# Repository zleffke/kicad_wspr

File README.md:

# kicad_wspr
KiCAD designs for WSPR Transmitters

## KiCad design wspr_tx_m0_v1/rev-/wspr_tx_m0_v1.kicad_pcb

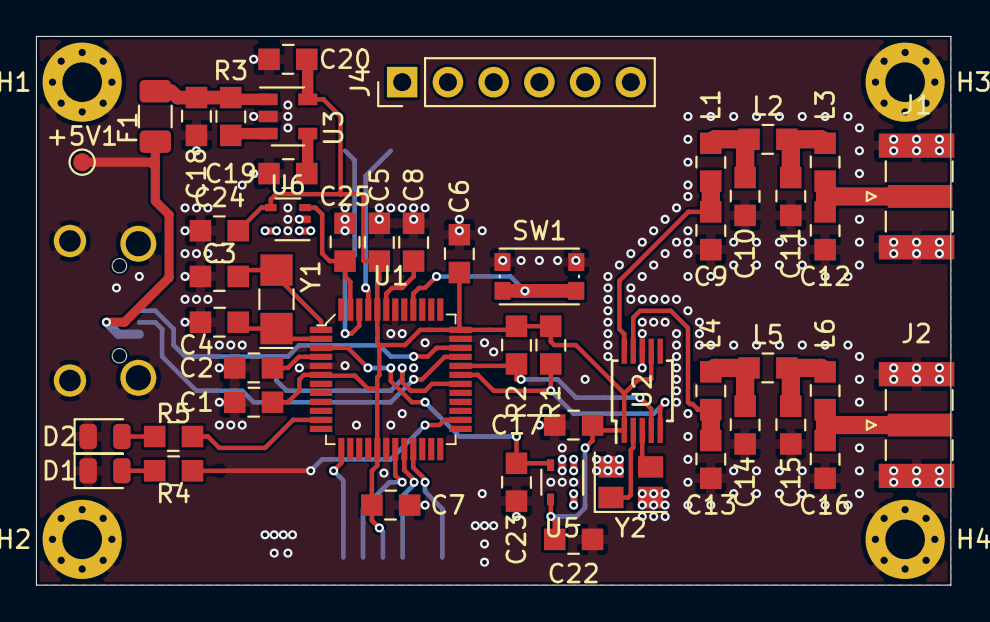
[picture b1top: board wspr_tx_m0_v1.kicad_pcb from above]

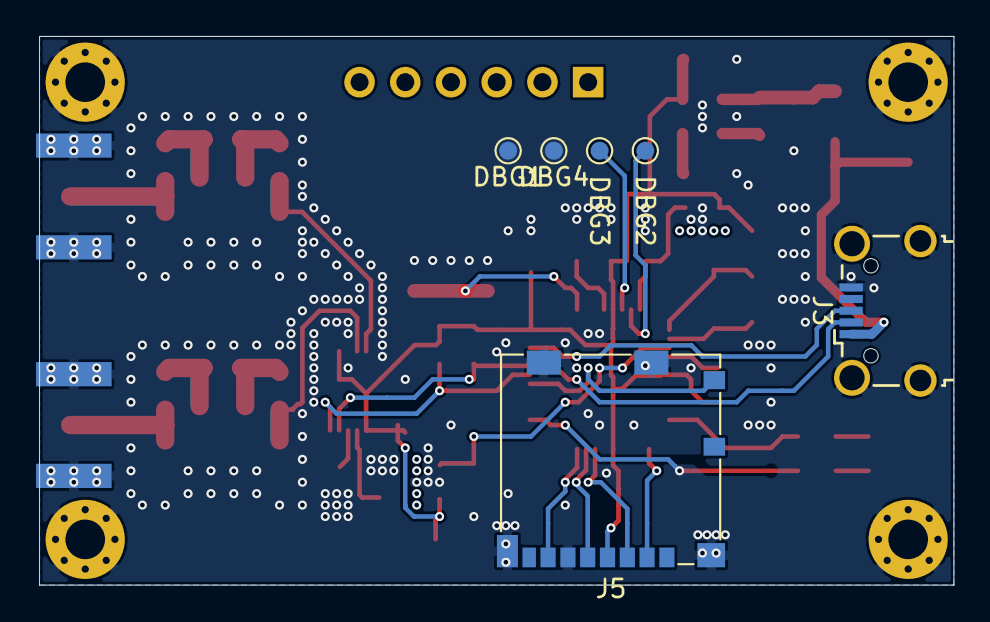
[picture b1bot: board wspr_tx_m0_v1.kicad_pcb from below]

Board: 2 copper layers, 50.8 x 30.5 mm, 60 parts (6 on the bottom side), 38 nets.

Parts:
+5V1: +5V; TestPoint_Pad_D1.0mm
C1, C2, C5, C6, C7, C8, C17, C19, C20, C22, C23, C24, C25: 1uF; 0805
C3, C4: 22pF; 0805
C9, C10, C11, C12, C13, C14, C15, C16: C; 0805
C18: 10uF; 0805
D1: RED; LED_0805_2012Metric
D2: GRN; LED_0805_2012Metric
DBG1: VREF; TestPoint_Pad_D1.0mm
DBG2: SWDIO; TestPoint_Pad_D1.0mm
DBG3: SWCLK; TestPoint_Pad_D1.0mm
DBG4: GND; TestPoint_Pad_D1.0mm
F1: Polyfuse; Fuse_1206_3216Metric
H1, H2, H3, H4: MountingHole_Pad; MountingHole_2.2mm_M2_Pad_Via
J1: RF1; SMA_Samtec_SMA-J-P-X-ST-EM1_EdgeMount
J2: RF2; SMA_Samtec_SMA-J-P-X-ST-EM1_EdgeMount
J3: USB_B_Micro; USB_Micro-B_Wuerth_629105150521_CircularHoles
J4: Conn_01x06_Male; PinHeader_1x06_P2.54mm_Vertical
J5: Micro_SD_Card_Det; microSD_HC_Molex_104031-0811
L1, L2, L3, L4, L5, L6: L; 0805
R1, R2: 4.7k; 0805
R3: 100k; 0805
R4, R5: 2.2k; 0805
SW1: SW_Push; SW_Push_1P1T_NO_CK_KMR2
U1: ATSAMD21G18A-AUT; TQFP-48_7x7mm
U2: Si5351A-B-GT; MSOP-10_3x3mm_P0.5mm
U3: SPX3819M5-L-3-3; SOT-23-5
U5, U6: MCP9700AT-ELT; SOT-353_SC-70-5
Y1: Crystal; Crystal_SMD_G8-2Pin_3.2x1.5mm_HandSoldering
Y2: Crystal_GND24; Crystal_SMD_Abracon_ABM8G-4Pin_3.2x2.5mm

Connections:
+3V3: C1.1, C5.1, C6.1, C7.1, C17.2, C20.1, C22.2, C24.2, DBG1.1, J5.4, R1.2, R2.2, U1.6, U1.17, U1.36, U1.44, U2.1, U2.7, U3.5, U5.4, U6.4
+5V: C18.1, F1.1, R3.2, U3.1
/A0: C23.2, U1.3, U5.3
/A5: C25.2, U1.47, U6.3
/AREF: C2.1, U1.4
/D7: J5.10, U1.30
/D8: R5.2, U1.11
/D13: R4.2, U1.26
/D+: J3.3, U1.34
/D-: J3.2, U1.33
/LPF Filters/RF1_IN: C9.1, L1.1, U2.10
/LPF Filters/RF1_OUT: C12.1, J1.1, L3.2
/LPF Filters/RF2_IN: C13.1, L4.1, U2.9
/LPF Filters/RF2_OUT: C16.1, J2.1, L6.2
/MISO: J5.7, U1.21
/MOSI: J5.3, U1.19
/SCK: J5.5, U1.20
/SCL: R2.1, U1.32, U2.4
/SDA: R1.1, U1.31, U2.5
/SD_CS: J5.2, U1.13
/SWCLK: DBG3.1, U1.45
/SWDIO: DBG2.1, U1.46
/~RESET: SW1.1, U1.40
GND: C1.2, C2.2, C3.2, C4.2, C5.2, C6.2, C7.2, C8.2, C9.2, C10.2, C11.2, C12.2, C13.2, C14.2, C15.2, C16.2, C17.1, C18.2, C19.2, C20.2, C22.1, C23.1, C24.1, C25.1, D1.1, D2.1, DBG4.1, H1.1, H2.1, H3.1, H4.1, J1.2, J2.2, J3.5, J3.6, J5.6, J5.11, SW1.2, U1.5, U1.18, U1.35, U1.42, U2.8, U3.2, U5.2, U6.2, Y2.2, Y2.4
unnamed: +5V1.1, F1.2, J3.1
unnamed: C3.1, U1.1, Y1.2
unnamed: C4.1, U1.2, Y1.1
unnamed: C8.1, U1.43
unnamed: C10.1, L1.2, L2.1
unnamed: C11.1, L2.2, L3.1
unnamed: C14.1, L4.2, L5.1
unnamed: C15.1, L5.2, L6.1
unnamed: C19.1, U3.4
unnamed: D1.2, R4.1
unnamed: D2.2, R5.1
unnamed: R3.1, U3.3
unnamed: U2.2, Y2.1
unnamed: U2.3, Y2.3

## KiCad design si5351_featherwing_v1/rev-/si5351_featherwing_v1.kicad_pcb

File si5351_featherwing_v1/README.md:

# si5351_featherwing_v1
* Si5351 breakout board in Adafruit Feather form factor.
* Basically an Si5351 breakout board with Low Pass Filters between clk0 and clk1 and the SMA connectors. 
* LPFs are bypassable if external filtering is used.
* This specific version was designed to work with an [Adafruit Feather M0 Adalogger](https://www.adafruit.com/product/2796) with reference to pinouts, interrupts, etc.  May be applicable to other feathers, but the M0 Adalogger was the primary focus.
* The current version of the design also expects an Ultimate GPS featherwing (for timing alignment).

#### Revision History
| Date     | Revision | Note  |
|----------|----------|-------|
| 20200429 | rev-     | Version was submitted to osh park for first prototypes |

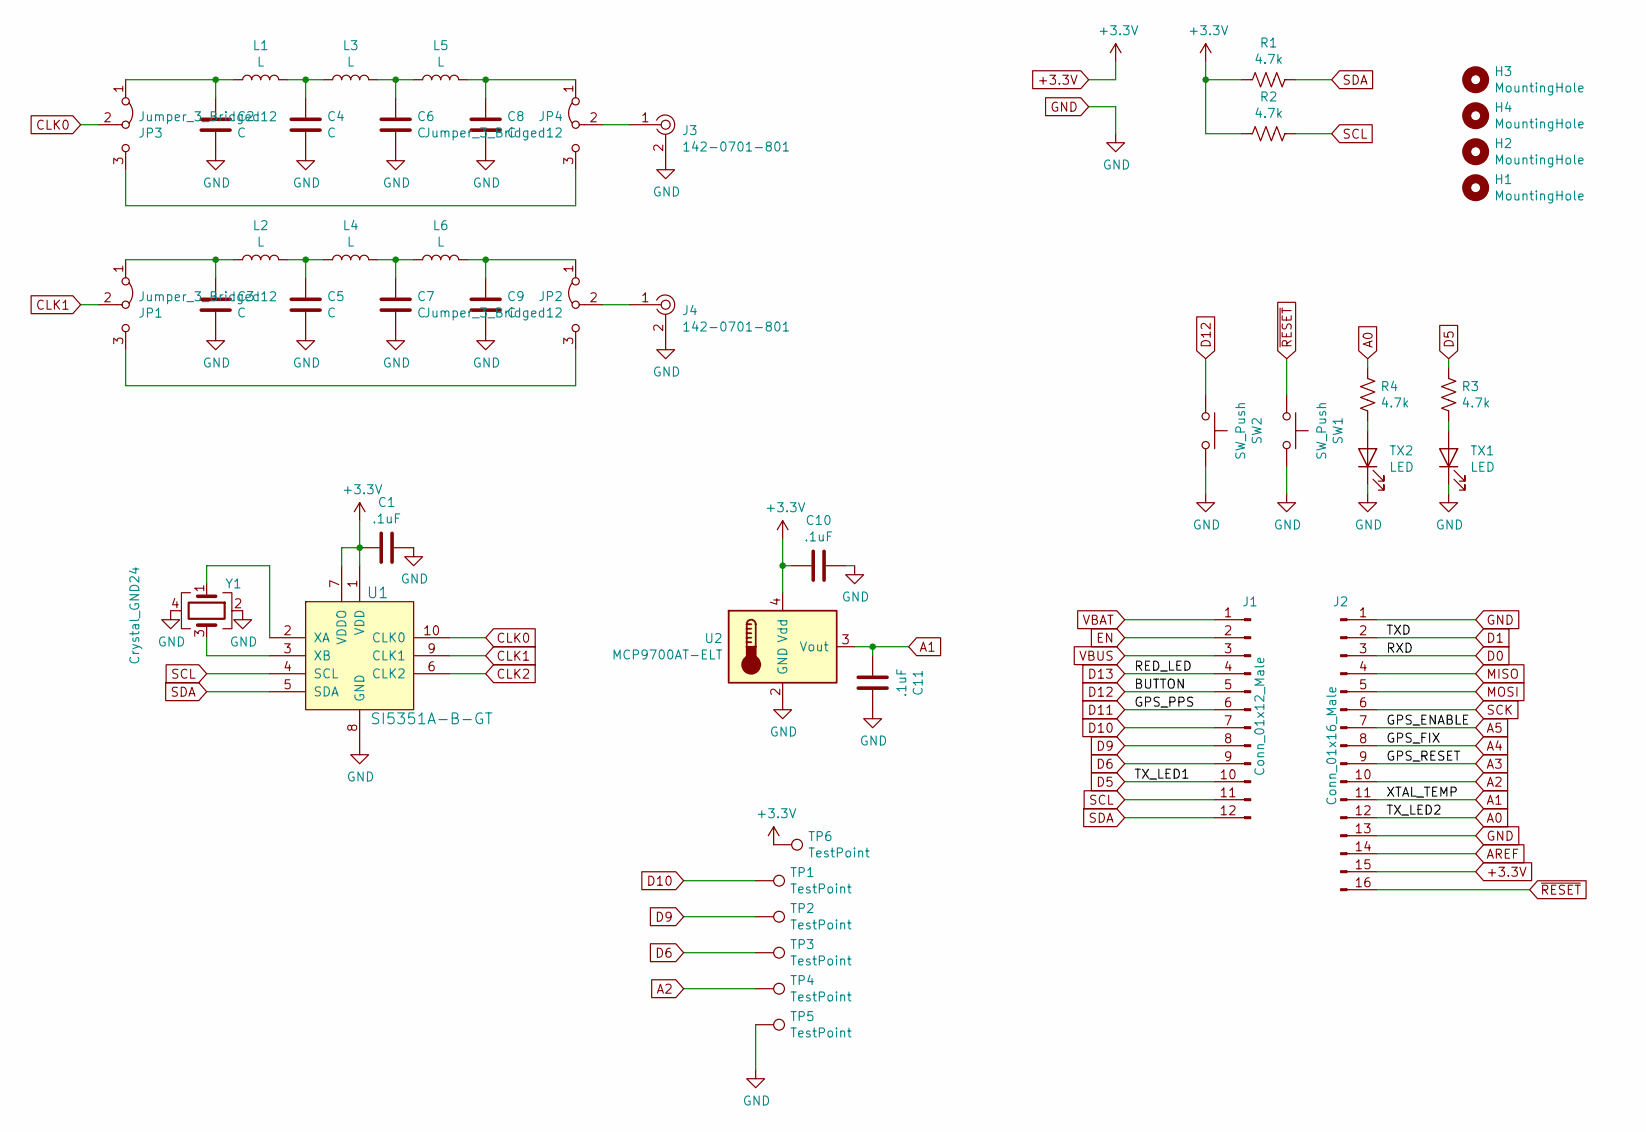
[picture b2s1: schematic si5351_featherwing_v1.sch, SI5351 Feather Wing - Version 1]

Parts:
C1, C10, C11: .1uF; 0805
C2, C3, C4, C5, C6, C7, C8, C9: C; 0805
H1, H2, H3, H4: MountingHole; MountingHole_2.5mm
J1: Conn_01x12_Male; PinHeader_1x12_P2.54mm_Vertical
J2: Conn_01x16_Male; PinHeader_1x16_P2.54mm_Vertical
J3, J4: 142-0701-801; RF_SMA_BoardEdge_142-0701-801; MPN 142-0701-801; Digi-Key_PN J502-ND
JP1, JP2, JP3, JP4: Jumper_3_Bridged12; SolderJumper-3_P1.3mm_Open_RoundedPad1.0x1.5mm_NumberLabels
L1, L2, L3, L4, L5, L6: L; 0805
R1, R2, R3, R4: 4.7k; 0805
SW1, SW2: SW_Push; SW_Push_1P1T_NO_CK_KMR2
TP1, TP2, TP3, TP4, TP5, TP6: TestPoint; TestPoint_Pad_D1.0mm
TX1, TX2: LED; LED_0805_2012Metric
U1: SI5351A-B-GT; MSOP-10_W3mm; MPN SI5351A-B-GT; Digi-Key_PN 336-2399-5-ND
U2: MCP9700AT-ELT; SOT-353_SC-70-5
Y1: Crystal_GND24; Crystal_SMD_Abracon_ABM8G-4Pin_3.2x2.5mm

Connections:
+3.3V: C1.2, C10.2, J2.15, R1.2, R2.2, TP6.1, U1.1 (VDD), U1.7 (VDDO), U2.4 (Vdd)
A0: J2.12, R4.2
A1: C11.2, J2.11, U2.3 (Vout)
A2: J2.10, TP4.1
A3: J2.9
A4: J2.8
A5: J2.7
AREF: J2.14
CLK0: JP3.2 (C), U1.10 (CLK0)
CLK1: JP1.2 (C), U1.9 (CLK1)
CLK2: U1.6 (CLK2)
D0: J2.3
D1: J2.2
D5: J1.10, R3.2
D6: J1.9, TP3.1
D9: J1.8, TP2.1
D10: J1.7, TP1.1
D11: J1.6
D12: J1.5, SW2.1
D13: J1.4
EN: J1.2
GND: C1.1, C2.2, C3.2, C4.2, C5.2, C6.2, C7.2, C8.2, C9.2, C10.1, C11.1, J2.1, J2.13, J3.2, J4.2, SW1.2, SW2.2, TP5.1, TX1.1 (K), TX2.1 (K), U1.8 (GND), U2.2 (GND), Y1.2, Y1.4
MISO: J2.4
MOSI: J2.5
unnamed: C2.1, JP3.1 (A), L1.1
unnamed: C3.1, JP1.1 (A), L2.1
unnamed: C4.1, L1.2, L3.1
unnamed: C5.1, L2.2, L4.1
unnamed: C6.1, L3.2, L5.1
unnamed: C7.1, L4.2, L6.1
unnamed: C8.1, JP4.1 (A), L5.2
unnamed: C9.1, JP2.1 (A), L6.2
unnamed: J3.1, JP4.2 (C)
unnamed: J4.1, JP2.2 (C)
unnamed: JP1.3 (B), JP2.3 (B)
unnamed: JP3.3 (B), JP4.3 (B)
unnamed: R3.1, TX1.2 (A)
unnamed: R4.1, TX2.2 (A)
unnamed: U1.2 (XA), Y1.1
unnamed: U1.3 (XB), Y1.3
SCK: J2.6
SCL: J1.11, R2.1, U1.4 (SCL)
SDA: J1.12, R1.1, U1.5 (SDA)
VBAT: J1.1
VBUS: J1.3
~RESET: J2.16, SW1.1

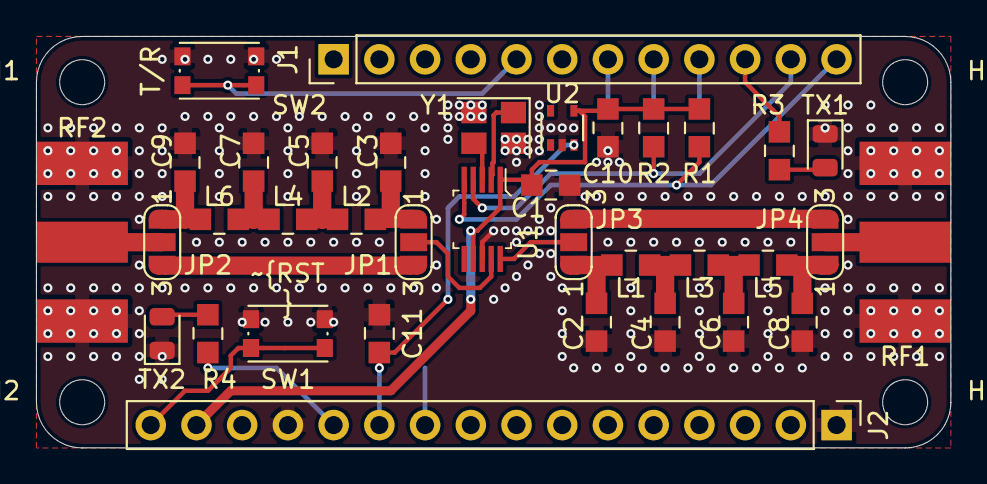
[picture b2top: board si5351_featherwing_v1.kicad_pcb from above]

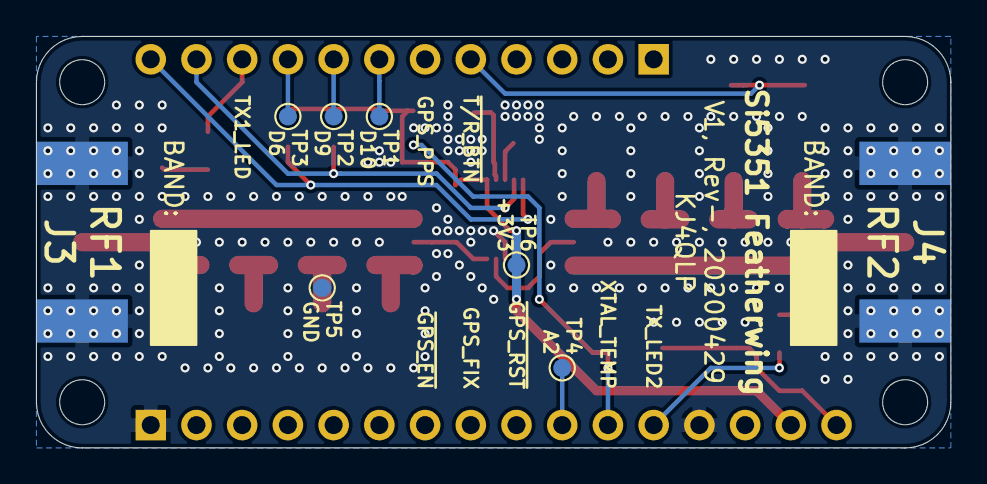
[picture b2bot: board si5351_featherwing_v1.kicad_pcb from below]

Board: 2 copper layers, 50.8 x 22.9 mm, 46 parts (6 on the bottom side), 31 nets.

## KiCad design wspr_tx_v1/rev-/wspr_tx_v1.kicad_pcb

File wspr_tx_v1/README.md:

# kicad_wspr_tx_v1
Basically an Si5351 breakout board with Low Pass Filters between all three clock outputs and the SMA connectors.

Taken from [Adafruit Si5351 Breakout EagleCAD design](https://github.com/adafruit/Adafruit-Si5351A-Clock-Generator-Breakout-PCB) but ported to KiCAD and LPFs added.

This version was designed but not actually built - 2020424

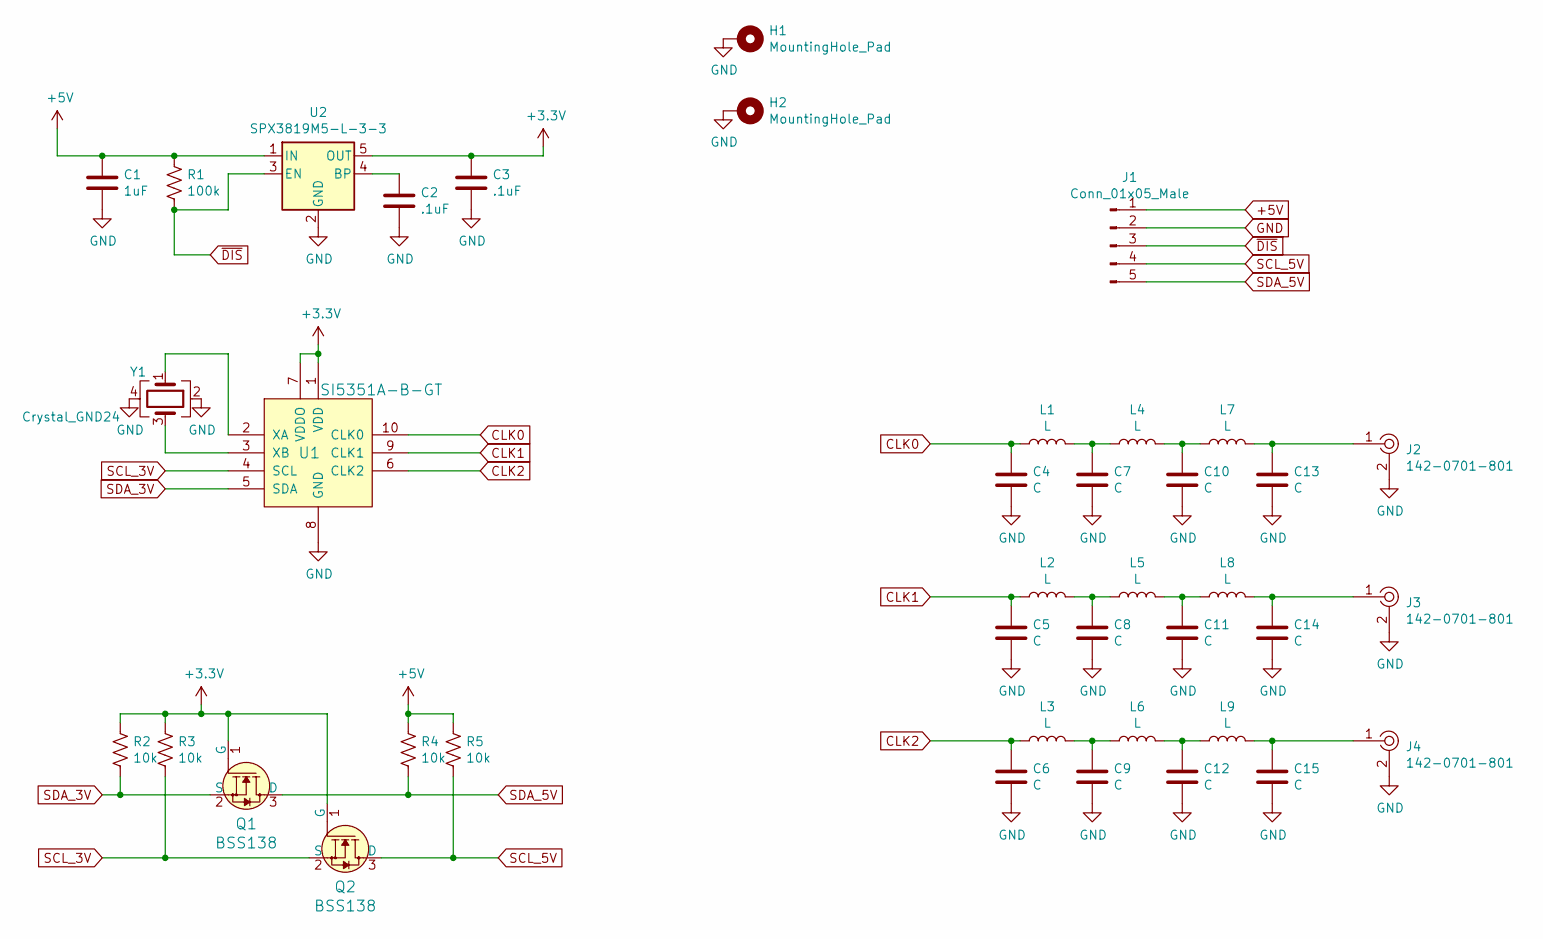
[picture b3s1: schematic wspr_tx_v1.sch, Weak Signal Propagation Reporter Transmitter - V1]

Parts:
C1: 1uF; 0805
C2, C3: .1uF; 0805
C4, C5, C6, C7, C8, C9, C10, C11, C12, C13, C14, C15: C; 0805
H1, H2: MountingHole_Pad; MountingHole_3.2mm_M3_Pad_Via
J1: Conn_01x05_Male; PinHeader_1x05_P2.54mm_Vertical
J2, J3, J4: 142-0701-801; RF_SMA_BoardEdge_142-0701-801; MPN 142-0701-801; Digi-Key_PN J502-ND
L1, L2, L3, L4, L5, L6, L7, L8, L9: L; 0805
Q1, Q2: BSS138; SOT-23-3; MPN BSS138; Digi-Key_PN BSS138CT-ND
R1: 100k; 0805
R2, R3, R4, R5: 10k; 0805
U1: SI5351A-B-GT; MSOP-10_W3mm; MPN SI5351A-B-GT; Digi-Key_PN 336-2399-5-ND
U2: SPX3819M5-L-3-3; SOT-23-5
Y1: Crystal_GND24; Crystal_SMD_3225-4Pin_3.2x2.5mm

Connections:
+3V3: C3.1, Q1.1 (G), Q2.1 (G), R2.1, R3.1, U1.1 (VDD), U1.7 (VDDO), U2.5 (OUT)
+5V: C1.1, J1.1, R1.1, R4.1, R5.1, U2.1 (IN)
CLK0: C4.1, L1.1, U1.10 (CLK0)
CLK1: C5.1, L2.1, U1.9 (CLK1)
CLK2: C6.1, L3.1, U1.6 (CLK2)
GND: C1.2, C2.2, C3.2, C4.2, C5.2, C6.2, C7.2, C8.2, C9.2, C10.2, C11.2, C12.2, C13.2, C14.2, C15.2, H1.1, H2.1, J1.2, J2.2, J3.2, J4.2, U1.8 (GND), U2.2 (GND), Y1.2, Y1.4
unnamed: C2.1, U2.4 (BP)
unnamed: C7.1, L1.2, L4.1
unnamed: C8.1, L2.2, L5.1
unnamed: C9.1, L3.2, L6.1
unnamed: C10.1, L4.2, L7.1
unnamed: C11.1, L5.2, L8.1
unnamed: C12.1, L6.2, L9.1
unnamed: C13.1, J2.1, L7.2
unnamed: C14.1, J3.1, L8.2
unnamed: C15.1, J4.1, L9.2
unnamed: U1.2 (XA), Y1.1
unnamed: U1.3 (XB), Y1.3
SCL_3V: Q2.2 (S), R3.2, U1.4 (SCL)
SCL_5V: J1.4, Q2.3 (D), R5.2
SDA_3V: Q1.2 (S), R2.2, U1.5 (SDA)
SDA_5V: J1.5, Q1.3 (D), R4.2
~DIS: J1.3, R1.2, U2.3 (EN)

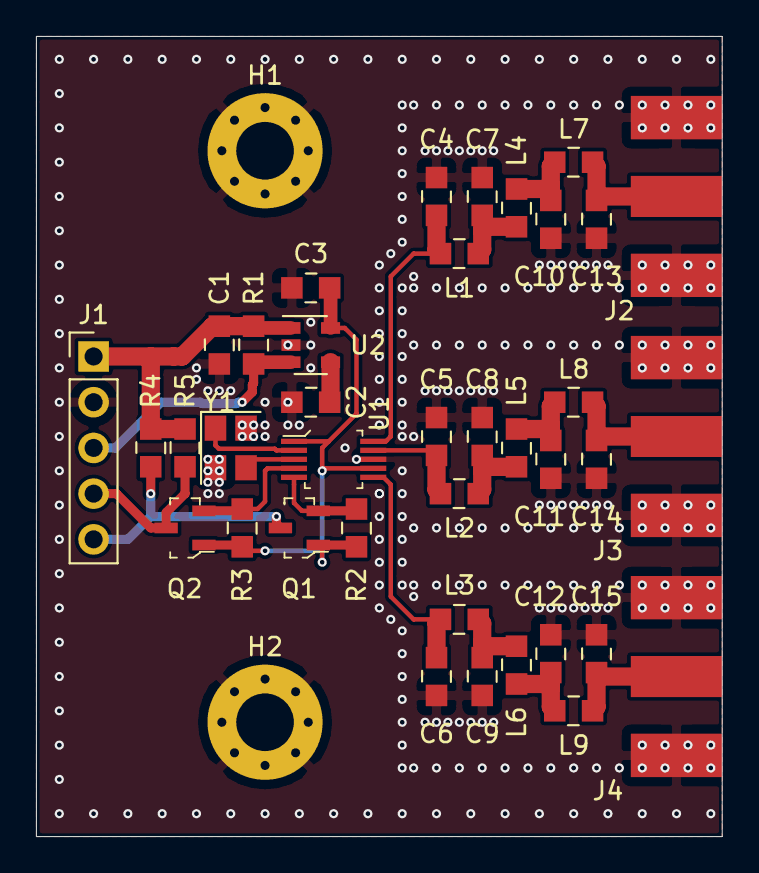
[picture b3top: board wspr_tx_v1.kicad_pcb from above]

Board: 2 copper layers, 38.1 x 44.5 mm, 40 parts (0 on the bottom side), 23 nets.

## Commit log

2020-04-24 initial mass commit of version 1, rev- design.
2020-04-29 commit of rev- featherwing design. this rev sent to osh park for prototyping.
2020-04-29 initial commit of integrated design, including MCU and Si5351 on single board.
2020-05-14 mass commit, lots of changes to m0 board, not functional yet. added schematic for featherwinf in PDF form.
2021-02-22 mass commit

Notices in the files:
si5351_featherwing_v1/rev-/si5351_featherwing_v1.kicad_pcb:
License: CC BY 4.0
si5351_featherwing_v1/rev-/si5351_featherwing_v1.sch:
creativecommons.org/licenses/by/4.0
